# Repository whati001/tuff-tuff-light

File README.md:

# 🚜 Wireless BLE Trailer Light System for Tractors

A robust, modular, and completely wireless trailer lighting system designed for agricultural machinery, utilizing BLE communication. 
Built on the **nRF52840 SoC** and developed with the **Zephyr RTOS**, this project includes custom-designed PCBs and 3D printed enclosures for reliable field use.
The choose design enables seamless connectivity without complicated pairing procedures and also allows to connect up to infinite receiver lights to a single sender.  

## ✨ Features

- 🔋 Battery-powered light modules (18650 x 4)
- 📡 BLE-based communication (nRF52840)
- 🔧 Built with **Zephyr RTOS**
- 🔦 Fully functional red+amber light cluster with wireless control
- 🧲 Magnetic mounting for quick install/removal
- 💻 Custom 3D printed cases and two custom-designed PCBs
- 🧠 Intelligent Power Saving (auto wakeup, no need to "switch" the light on)
---

## 📦 Project Structure
The project is structured as follows.
```
.
├── 3d/             # 3d printer files
├── applications/ 
│ ├── ttl_sender/   # ttl sender code
│ └── ttl_receiver/ # ttl receiver code
├── boards/         # custom boards definition
├── pcb/            # custom pcb KiCad files
...
└── README.md
```

---

## 🚀 Getting Started

### 🛠️ Requirements

- [Zephyr SDK](https://docs.zephyrproject.org/latest/develop/getting_started/index.html)
- [West Tool](https://docs.zephyrproject.org/latest/develop/west/index.html)
- Python 3.8+
- USB debugger (J-Link or compatible)
- Custom PCB (JLC PCB + self assembly)

### 📥 1. Clone and Initialize
First we need to initiate a python environment and install west. Afterwards, we initiate the Zephyr workspace.
```bash
python -m venv ./env
<activate venv>
pip install west
west init -m https://github.com/whati001/tuff-tuff-light tuff_tuff_light
cd tuff_tuff_light
west update
```

### 🧪 2. Build the Firmware
Navigate into the workspace directory and run:

```
# build sender
west build -b ttlv1_pa/nrf52840 ttl/applications/ttl_sender

# build receiver
west build -b ttlv1/nrf52840 ttl/applications/ttl_sender
```

### 🔌 3. Flash the Devices

Connect your debugger and run:

```
west flash
```

## 📡 System Overview

Transmitter: Reads trailer socket signals and broadcasts light commands via BLE.
Receiver Modules: Interpret BLE commands and control LEDs accordingly.

## 🧩 Hardware Details

* PCBs
  * TX Board: Reads 4-pin trailer plug input, handles BLE communication.
  * RX Board: Contains BLE radio, LED drivers, battery power management.

* Enclosures
  * All parts are printed with PLA and designed for rugged outdoor use.
  * STL/STEP files are included in the 3d/ directory.

## 🧪 Testing and Validation

The project aims just to be a minimal viable project (MVP), so there is not much testing included.

## 📃 License

This project is licensed under the MIT License. See the LICENSE file for details.

## 🤝 Contributing

Contributions are welcome! If you'd like to add features (e.g., low battery warnings, OTA updates), feel free to open a PR or issue.
If you are interested to turn this MVP into a real project, please get in touch with me. 

## 🧭 Next Steps

Here are a few ideas and enhancements planned or recommended for future development:

🔋 Battery Charging
Currently, power is restored by manually replacing the 18650 batteries. The proposed improvement is to integrate a charging circuit directly into the 3D-printed enclosure, enabling in-place recharging and eliminating the need to open the housing. At the same time, the design would retain compatibility with swappable battery modules, allowing a quick base replacement in scenarios where charging time is a limiting factor.

🚦 Expanded Signal Set
Extend support for additional signal inputs from the standard 7-pin trailer connector, including reverse, brake, fog lights, and more. Furthermore, the system’s modular architecture enables the integration of entirely new light types, such as side marker lights (e.g., white delimiting lights along the trailer’s sides), enhancing both functionality and visibility.

🌧️ Weatherproofing Enhancements
Improve gasket seals in the 3D printed case and verify IP rating in outdoor environments.

📘 Documentation Expansion
Add detailed firmware architecture docs and schematic walkthroughs.

## 📬 Contact

For questions, suggestions, or demo requests, feel free to contact [whati001@outlook.com] or open a GitHub issue

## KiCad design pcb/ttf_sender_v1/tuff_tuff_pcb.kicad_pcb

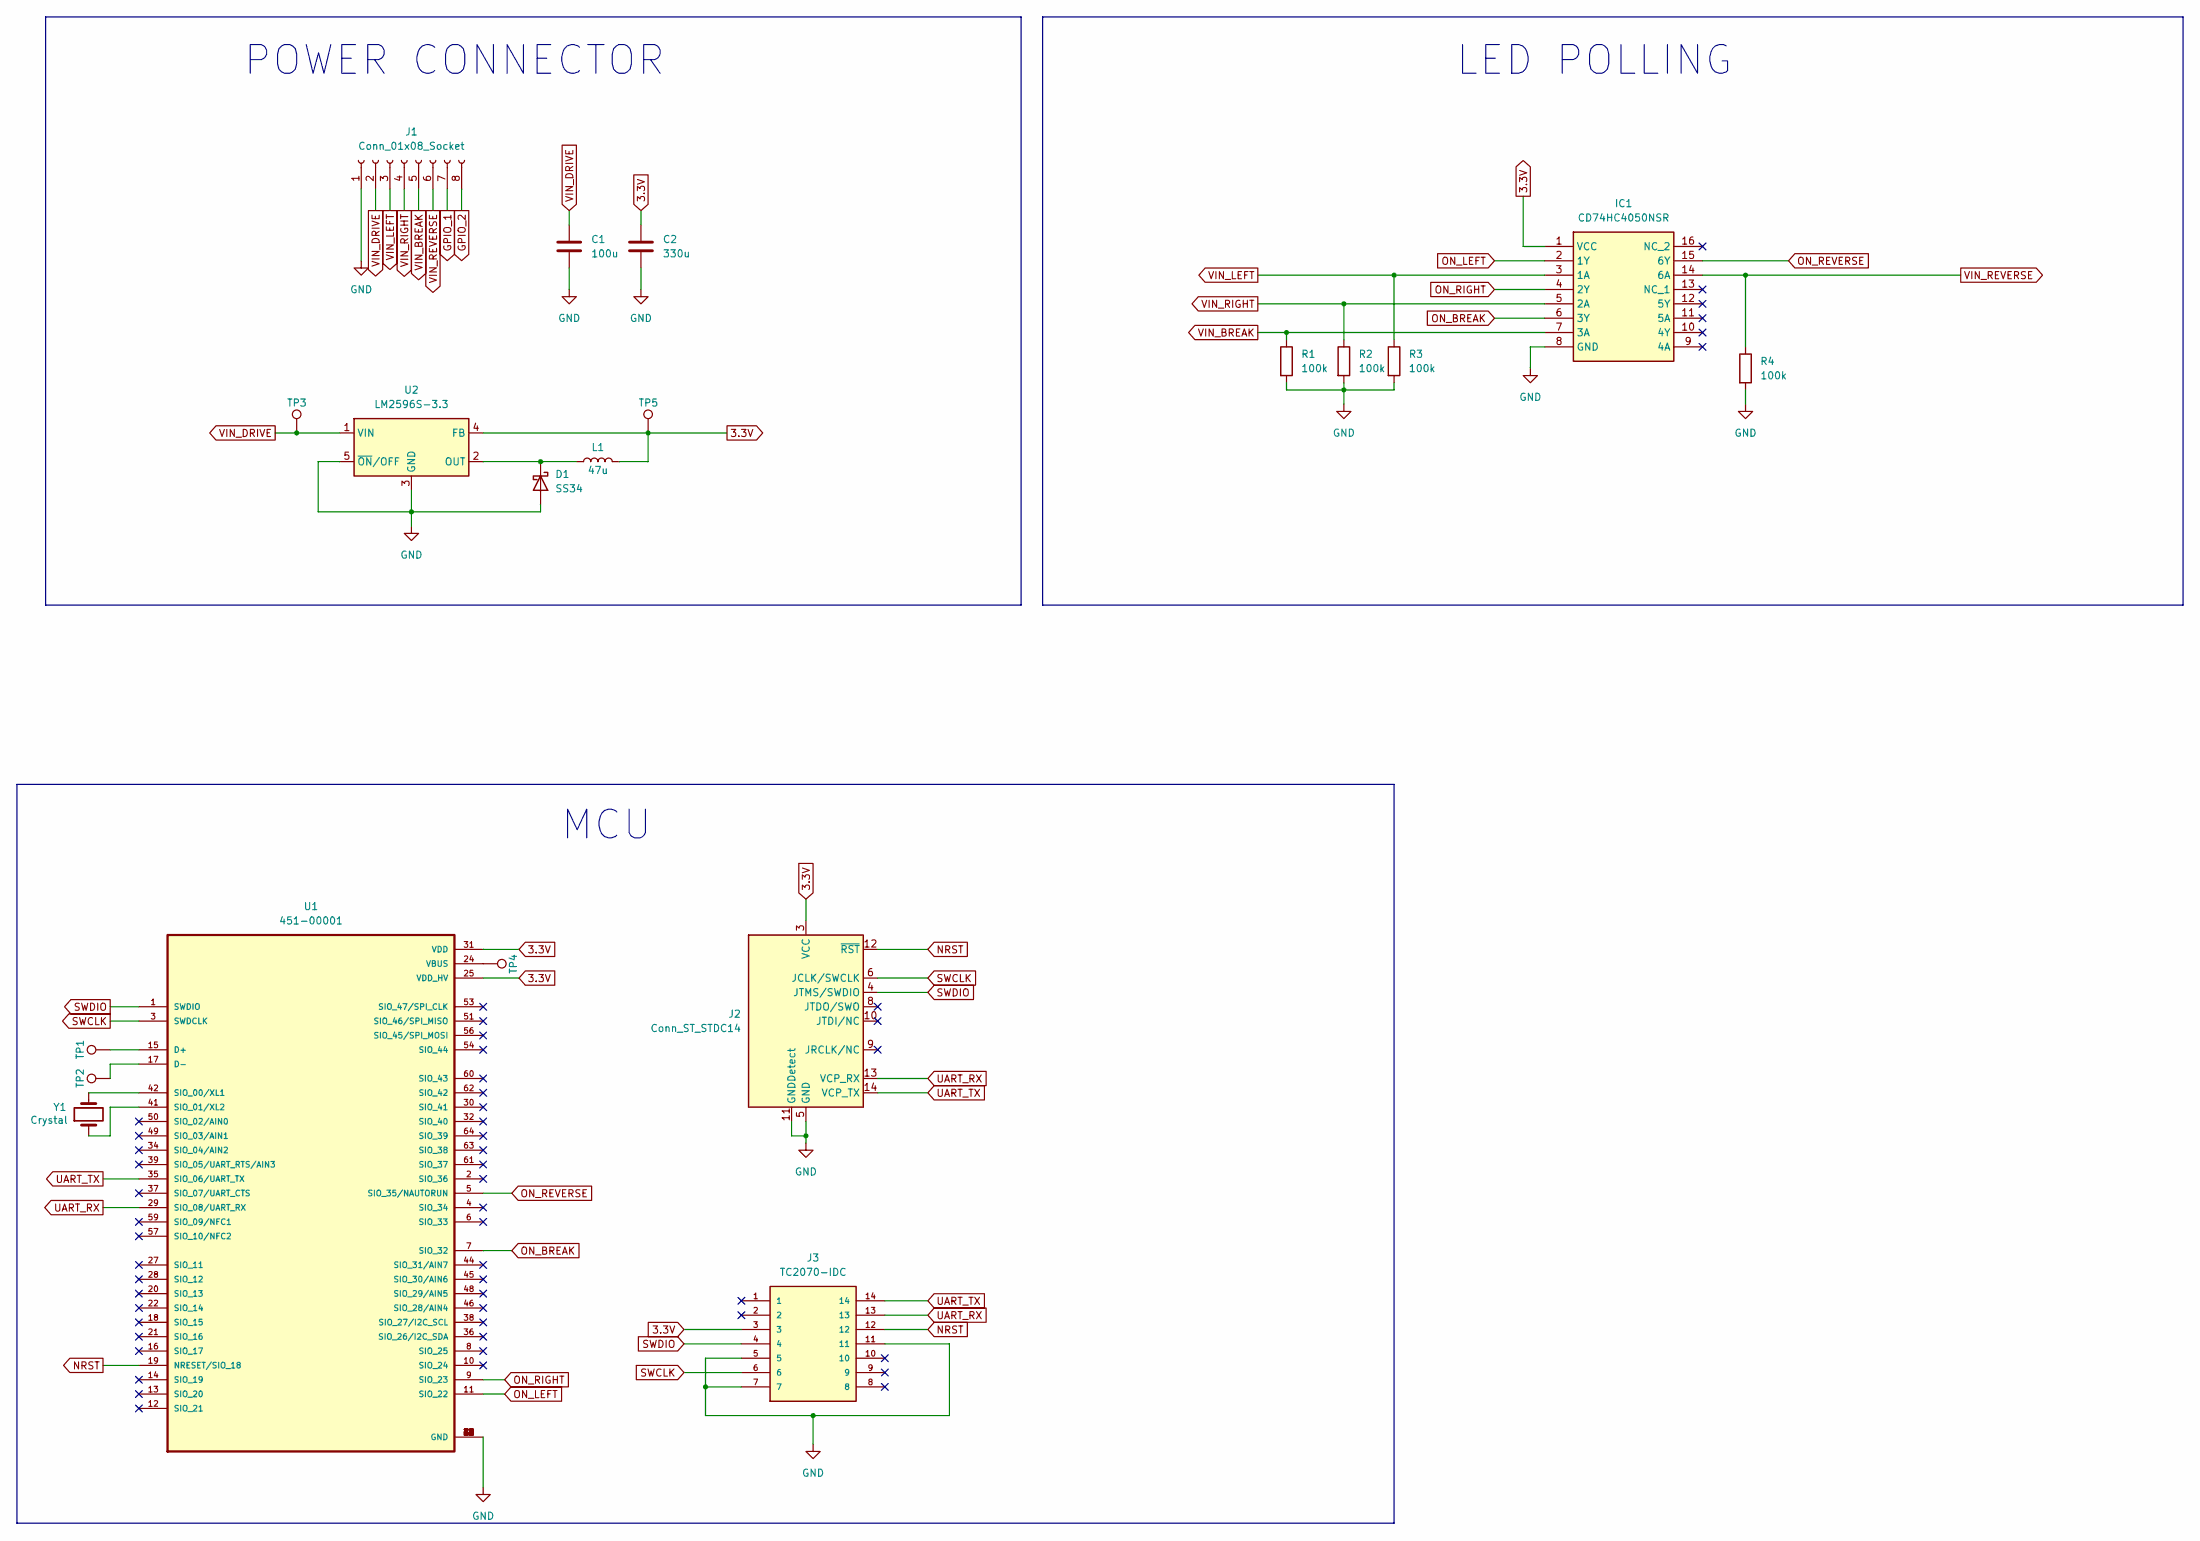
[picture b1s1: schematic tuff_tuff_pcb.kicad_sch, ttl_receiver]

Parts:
C1: 100u; CP_Radial_D5.0mm_P2.00mm; Part# at home
C2: 330u; CP_Radial_D8.0mm_P3.80mm; Part# at home
D1: SS34; D_SMA; LCSC C8678
IC1: CD74HC4050NSR; TSSOP-16_4.4x5mm_P0.65mm; Mouser Part Number 595-CD74HC4050NSR
J1: Conn_01x08_Socket; PinHeader_1x08_P2.00mm_Vertical
J2: Conn_ST_STDC14; PinHeader_2x07_P1.27mm_Vertical_SMD; LCSC C41370775
J3: TC2070-IDC; TAG-CONNECT_TC2070-IDC
L1: 47u; L_12x12mm_H8mm; LCSC C2041853
R1, R2, R3: 100k; C_1206_3216Metric_Pad1.33x1.80mm_HandSolder; LCSC C17900
R4: 100k; C_1206_3216Metric_Pad1.33x1.80mm_HandSolder; LCSC Part# C4107364
TP1, TP2, TP3, TP4, TP5: TestPoint; TestPoint_Pad_D2.0mm
U1: 451-00001; XCVR_451-00001; Mouser Part# 814-451-00002
U2: LM2596S-3.3; TO-263-5_TabPin3; LCSC C5186052
Y1: Crystal; Crystal_SMD_MicroCrystal_CC8V-T1A-2Pin_2.0x1.2mm; Mouser Part# 428-201410-MC01

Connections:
3.3V: C2.1, IC1.1 (VCC), J2.3 (VCC), J3.3, L1.2, TP5.1, U1.25 (VDD_HV), U1.31 (VDD), U2.4 (FB)
GND: C1.2, C2.2, D1.2 (A), IC1.8 (GND), J1.1, J2.5 (GND), J2.7 (GND), J2.11 (GNDDetect), J3.5, J3.7, J3.11, R1.2, R2.2, R3.2, R4.2, U1.0 (GND), U1.23 (GND), U1.26 (GND), U1.33 (GND), U1.40 (GND), U1.43 (GND), U1.47 (GND), U1.52 (GND), U1.55 (GND), U1.58 (GND), U1.65 (GND), U1.66 (GND), U1.67 (GND), U1.68 (GND), U1.69 (GND), U1.70 (GND), U1.71 (GND), U2.3 (GND), U2.5 (~ON/OFF)
GPIO_1: J1.7
GPIO_2: J1.8
NRST: J2.12 (~RST), J3.12, U1.19 (NRESET/SIO_18)
unnamed: D1.1 (K), L1.1, U2.2 (OUT)
unnamed: TP1.1, U1.15 (D+)
unnamed: TP2.1, U1.17 (D-)
unnamed: U1.42 (SIO_00/XL1), Y1.2
unnamed: U1.41 (SIO_01/XL2), Y1.1
unnamed: TP4.1, U1.24 (VBUS)
ON_BREAK: IC1.6 (3Y), U1.7 (SIO_32)
ON_LEFT: IC1.2 (1Y), U1.11 (SIO_22)
ON_REVERSE: IC1.15 (6Y), U1.5 (SIO_35/NAUTORUN)
ON_RIGHT: IC1.4 (2Y), U1.9 (SIO_23)
SWCLK: J2.6 (JCLK/SWCLK), J3.6, U1.3 (SWDCLK)
SWDIO: J2.4 (JTMS/SWDIO), J3.4, U1.1 (SWDIO)
UART_RX: J2.13 (VCP_RX), J3.13, U1.29 (SIO_08/UART_RX)
UART_TX: J2.14 (VCP_TX), J3.14, U1.35 (SIO_06/UART_TX)
VIN_BREAK: IC1.7 (3A), J1.5, R1.1
VIN_DRIVE: C1.1, J1.2, TP3.1, U2.1 (VIN)
VIN_LEFT: IC1.3 (1A), J1.3, R3.1
VIN_REVERSE: IC1.14 (6A), J1.6, R4.1
VIN_RIGHT: IC1.5 (2A), J1.4, R2.1

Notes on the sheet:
MCU
LED POLLING
POWER CONNECTOR

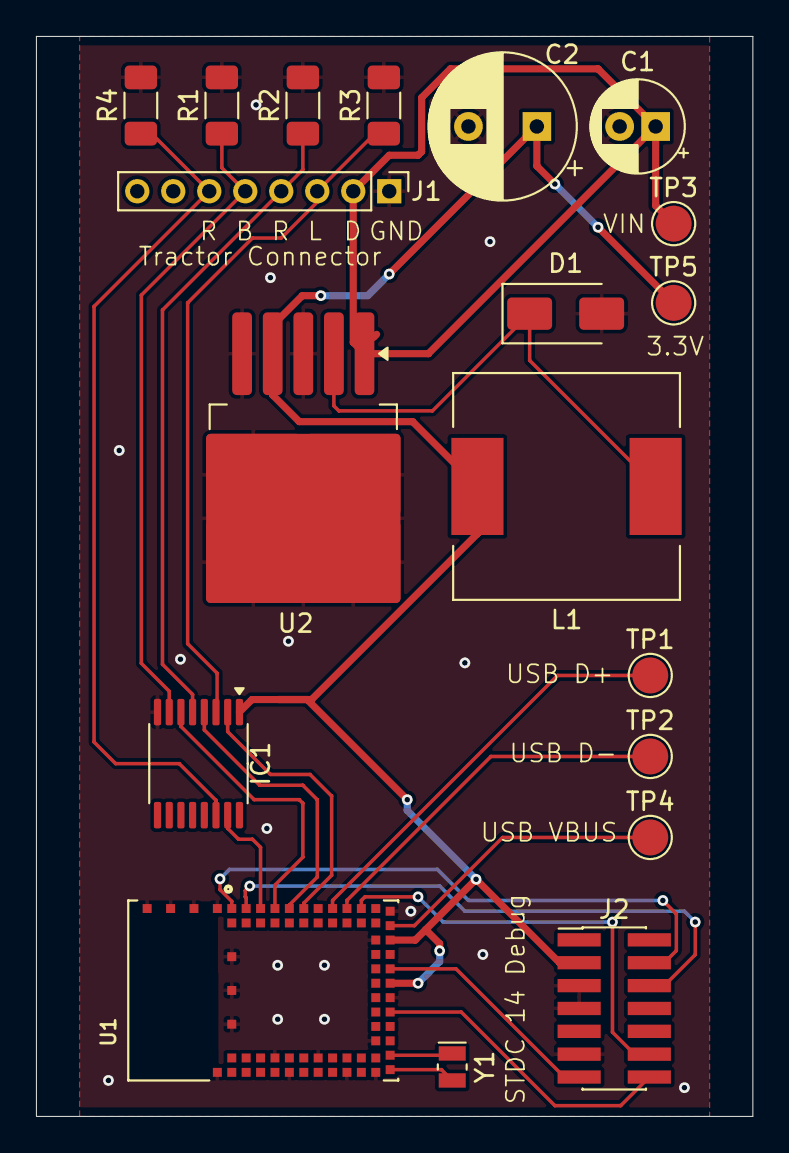
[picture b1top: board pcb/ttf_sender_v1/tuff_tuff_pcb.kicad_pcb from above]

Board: 2 copper layers, 39.8 x 60.0 mm, 19 parts (0 on the bottom side), 22 nets.

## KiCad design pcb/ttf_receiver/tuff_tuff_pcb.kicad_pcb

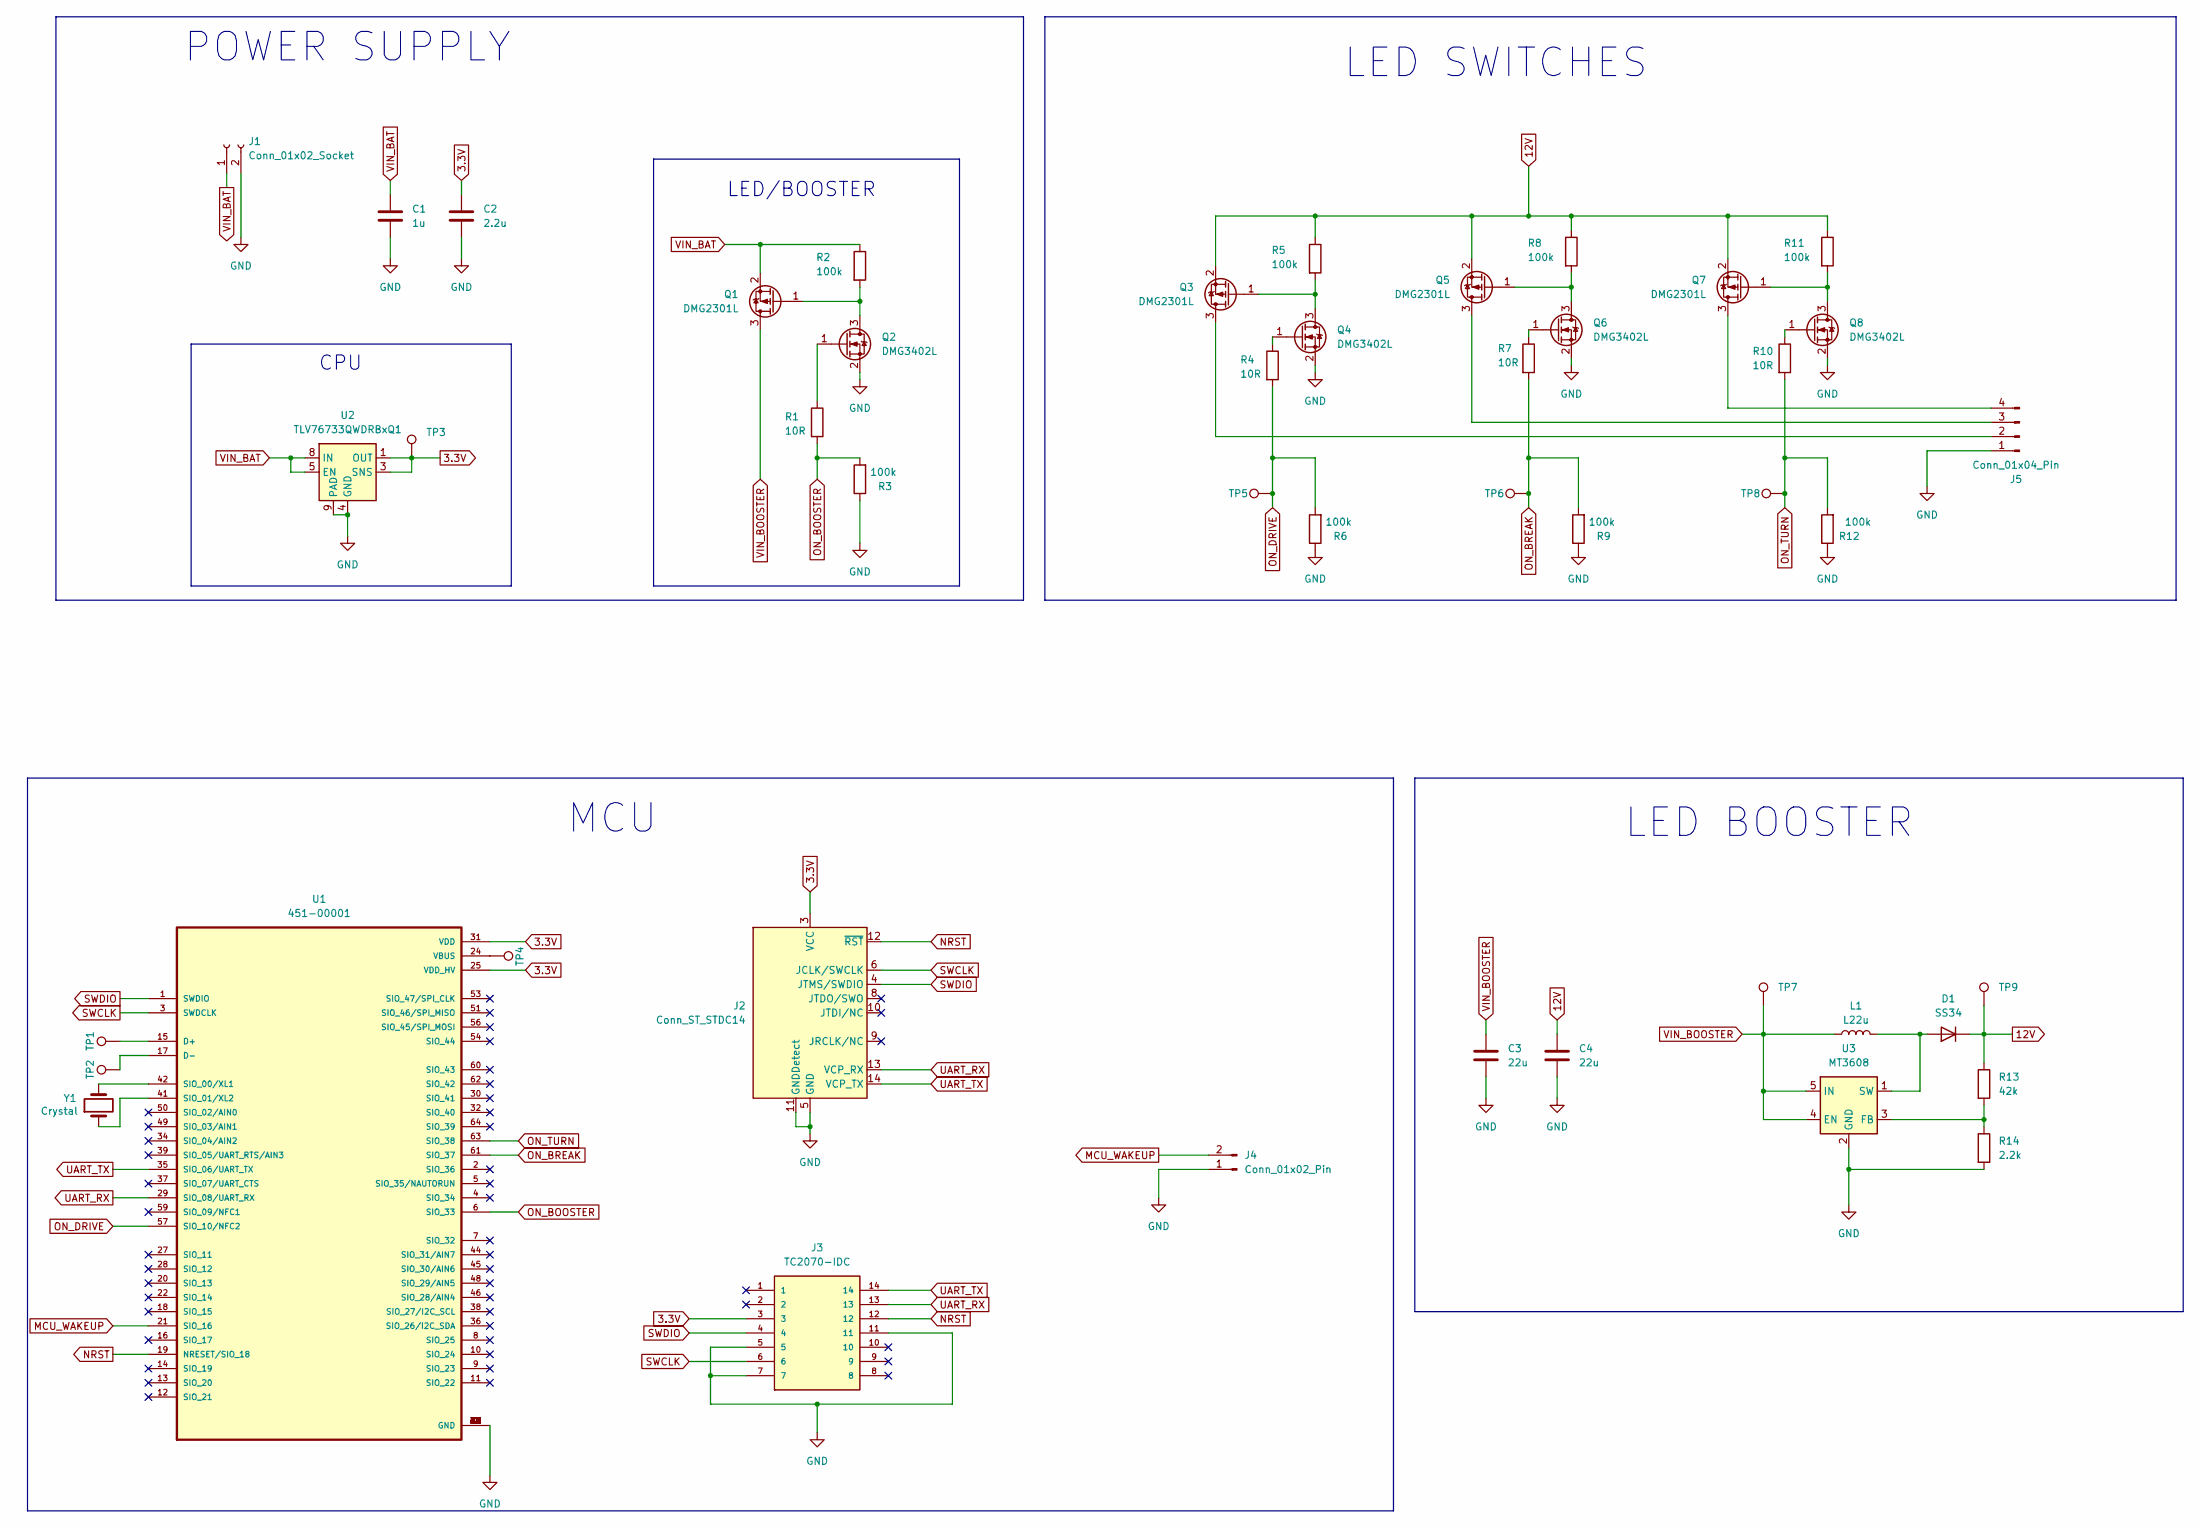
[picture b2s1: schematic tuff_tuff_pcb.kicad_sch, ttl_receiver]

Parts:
C1: 1u; C_1206_3216Metric_Pad1.33x1.80mm_HandSolder; LCSC C1848
C2: 2.2u; C_1206_3216Metric_Pad1.33x1.80mm_HandSolder; LCSC C50254
C3, C4: 22u; C_1206_3216Metric_Pad1.33x1.80mm_HandSolder; LCSC C12891
D1: SS34; D_SMA; LCSC C8678
J1: Conn_01x02_Socket; PinHeader_1x02_P2.54mm_Vertical
J2: Conn_ST_STDC14; PinHeader_2x07_P1.27mm_Vertical_SMD; LCSC C41370775
J3: TC2070-IDC; TAG-CONNECT_TC2070-IDC
J4: Conn_01x02_Pin; PinSocket_1x02_P2.54mm_Vertical
J5: Conn_01x04_Pin; PinHeader_1x04_P2.54mm_Vertical
L1: L22u; L_1210_3225Metric; LCSC C711136
Q1, Q3, Q5, Q7: DMG2301L; SOT-23; LCSC C102619
Q2, Q4, Q6, Q8: DMG3402L; SOT-23; LCSC C96614
R1, R4, R7, R10: 10R; R_1206_3216Metric_Pad1.30x1.75mm_HandSolder; LCSC C104606
R2, R3, R5, R6, R8, R9, R11, R12: 100k; R_1206_3216Metric_Pad1.30x1.75mm_HandSolder; LCSC C17900
R13: 42k; R_1206_3216Metric_Pad1.30x1.75mm_HandSolder; LCSC C229633
R14: 2.2k; R_1206_3216Metric_Pad1.30x1.75mm_HandSolder; LCSC C114933
TP1, TP2, TP3, TP4, TP5, TP6, TP8: TestPoint; TestPoint_Pad_D2.0mm
TP7: IN BOOSTER; TestPoint_Pad_D2.0mm
TP9: OUT BOOSTER; TestPoint_Pad_D2.0mm
U1: 451-00001; XCVR_451-00001; Mouser Part# 814-451-00002
U2: TLV76733QWDRBxQ1; SOP65P490X110-9N; LCSC C2873382
U3: MT3608; SOT-23-6; LCSC C84817
Y1: Crystal; Crystal_SMD_MicroCrystal_CC8V-T1A-2Pin_2.0x1.2mm; Mouser Part# 428-201410-MC01

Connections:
3.3V: C2.1, J2.3 (VCC), J3.3, TP3.1, U1.25 (VDD_HV), U1.31 (VDD), U2.1 (OUT), U2.3 (SNS)
12V: C4.1, D1.1 (K), Q3.2 (S), Q5.2 (S), Q7.2 (S), R5.1, R8.1, R11.1, R13.1, TP9.1
GND: C1.2, C2.2, C3.2, C4.2, J1.2, J2.5 (GND), J2.7 (GND), J2.11 (GNDDetect), J3.5, J3.7, J3.11, J4.1, J5.1, Q2.2 (S), Q4.2 (S), Q6.2 (S), Q8.2 (S), R3.1, R6.1, R9.1, R12.1, R14.2, U1.0 (GND), U1.23 (GND), U1.26 (GND), U1.33 (GND), U1.40 (GND), U1.43 (GND), U1.47 (GND), U1.52 (GND), U1.55 (GND), U1.58 (GND), U1.65 (GND), U1.66 (GND), U1.67 (GND), U1.68 (GND), U1.69 (GND), U1.70 (GND), U1.71 (GND), U2.4 (GND), U2.6 (GND), U2.9 (PAD), U3.2 (GND)
MCU_WAKEUP: J4.2, U1.21 (SIO_16)
NRST: J2.12 (~RST), J3.12, U1.19 (NRESET/SIO_18)
unnamed: D1.2 (A), L1.2, U3.1 (SW)
unnamed: J5.2, Q3.3 (D)
unnamed: J5.3, Q5.3 (D)
unnamed: J5.4, Q7.3 (D)
unnamed: Q1.1 (G), Q2.3 (D), R2.2
unnamed: Q2.1 (G), R1.1
unnamed: Q3.1 (G), Q4.3 (D), R5.2
unnamed: Q4.1 (G), R4.1
unnamed: Q5.1 (G), Q6.3 (D), R8.2
unnamed: Q6.1 (G), R7.1
unnamed: Q7.1 (G), Q8.3 (D), R11.2
unnamed: Q8.1 (G), R10.1
unnamed: TP1.1, U1.15 (D+)
unnamed: TP2.1, U1.17 (D-)
unnamed: U1.42 (SIO_00/XL1), Y1.2
unnamed: U1.41 (SIO_01/XL2), Y1.1
unnamed: TP4.1, U1.24 (VBUS)
unnamed: R13.2, R14.1, U3.3 (FB)
ON_BOOSTER: R1.2, R3.2, U1.6 (SIO_33); also elsewhere on the board
ON_BREAK: R7.2, R9.2, TP6.1, U1.61 (SIO_37)
ON_DRIVE: R4.2, R6.2, TP5.1, U1.57 (SIO_10/NFC2)
ON_TURN: R10.2, R12.2, TP8.1, U1.63 (SIO_38)
SWCLK: J2.6 (JCLK/SWCLK), J3.6, U1.3 (SWDCLK)
SWDIO: J2.4 (JTMS/SWDIO), J3.4, U1.1 (SWDIO)
UART_RX: J2.13 (VCP_RX), J3.13, U1.29 (SIO_08/UART_RX)
UART_TX: J2.14 (VCP_TX), J3.14, U1.35 (SIO_06/UART_TX)
VIN_BAT: C1.1, J1.1, Q1.2 (S), R2.1, U2.5 (EN), U2.8 (IN)
VIN_BOOSTER: C3.1, L1.1, Q1.3 (D), TP7.1, U3.4 (EN), U3.5 (IN)

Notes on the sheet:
LED/BOOSTER
LED BOOSTER
MCU
CPU
LED SWITCHES
POWER SUPPLY

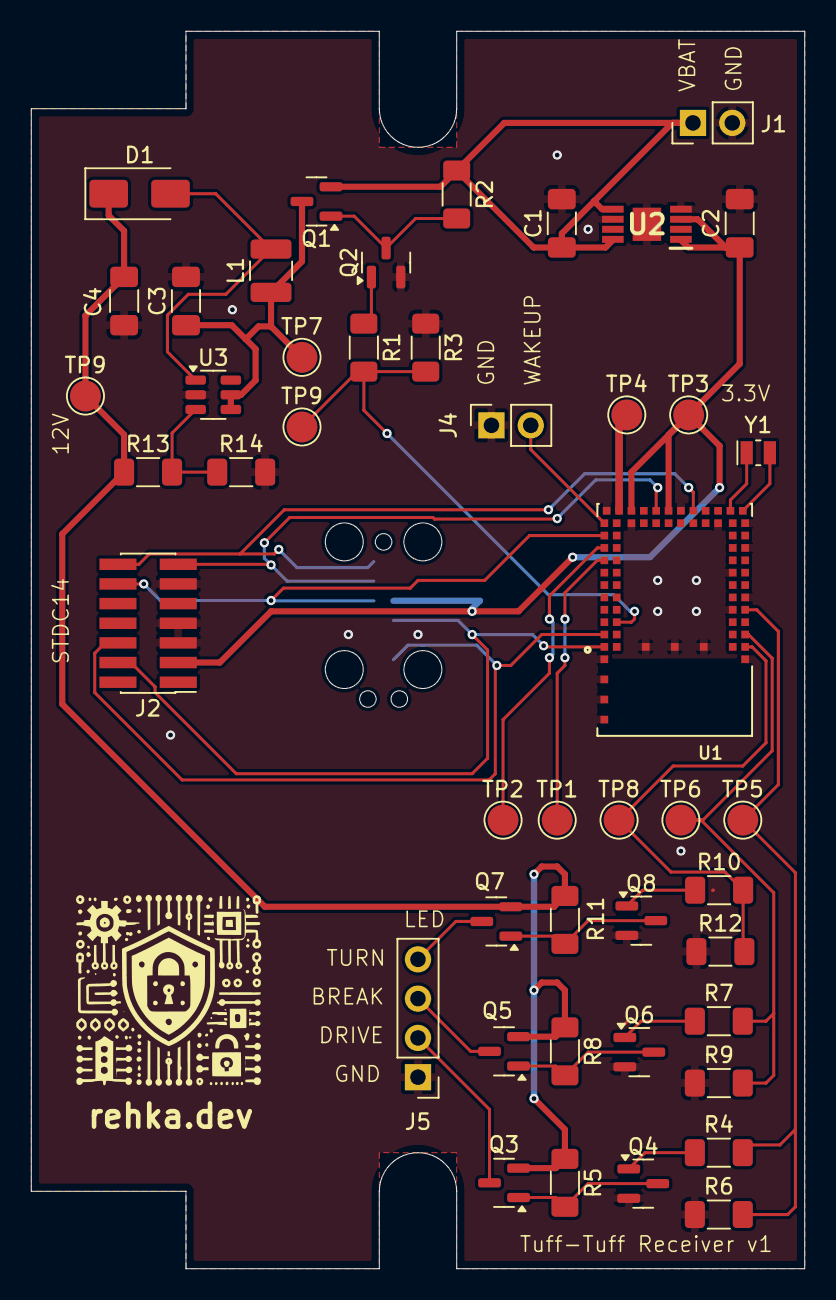
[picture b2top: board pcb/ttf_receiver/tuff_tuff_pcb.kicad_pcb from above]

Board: 2 copper layers, 50.0 x 80.0 mm, 47 parts (1 on the bottom side), 33 nets.

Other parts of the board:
TP9#2: ON BOOSTER; TestPoint_Pad_D2.0mm

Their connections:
ON_BOOSTER: TP9#2.1; also elsewhere on the board

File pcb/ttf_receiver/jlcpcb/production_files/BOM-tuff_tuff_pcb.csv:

Comment,Designator,Footprint,LCSC,Quantity
DMG2301L,"Q1,Q3,Q5,Q7",SOT-23,C102619,4
10R,"R1,R10,R4,R7",R_1206_3216Metric_Pad1.30x1.75mm_HandSolder,C104606,4
2.2k,R14,R_1206_3216Metric_Pad1.30x1.75mm_HandSolder,C114933,1
22u,"C3,C4",C_1206_3216Metric_Pad1.33x1.80mm_HandSolder,C12891,2
100k,"R11,R12,R2,R3,R5,R6,R8,R9",R_1206_3216Metric_Pad1.30x1.75mm_HandSolder,C17900,8
1u,C1,C_1206_3216Metric_Pad1.33x1.80mm_HandSolder,C1848,1
42k,R13,R_1206_3216Metric_Pad1.30x1.75mm_HandSolder,C229633,1
TLV76733QWDRBxQ1,U2,SOP65P490X110-9N,C2873382,1
Conn_ST_STDC14,J2,PinHeader_2x07_P1.27mm_Vertical_SMD,C41370775,1
2.2u,C2,C_1206_3216Metric_Pad1.33x1.80mm_HandSolder,C50254,1
Crystal,Y1,Crystal_SMD_MicroCrystal_CC8V-T1A-2Pin_2.0x1.2mm,C5142652,1
L22u,L1,L_1210_3225Metric,C711136,1
451-00001,U1,XCVR_451-00001,C7185357,1
MT3608,U3,SOT-23-6,C84817,1
SS34,D1,D_SMA,C8678,1
DMG3402L,"Q2,Q4,Q6,Q8",SOT-23,C96614,4
ON BOOSTER,TP9,TestPoint_Pad_D2.0mm,,1

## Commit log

2022-01-06 AK - added digital read
2022-01-07 AK - added cad and cleaned code
2022-01-07 AK - removed build
2022-01-07 AK - added build dir to gitignore
2022-01-08 AK - added peripheral dk poc code
2022-01-08 AK - renamed stage to state
2022-01-08 AK - added central poc code
2022-01-10 AK - added central interrupt listener
2022-01-11 AK - added interrupt support on central
2022-01-11 AK - disable some logging
2022-01-11 AK - added nrf52840dongle board overlay
2022-01-11 AK - added multilink
2022-01-11 AK - fixed issue6 use polling with 50ms interval on central
2022-01-29 AK - added vscode config and sourced out include files
2022-09-21 AK - refactored peripheral
2022-09-21 AK - added NO_HOST_STATE update to prevent wrong signals on the leds
2022-09-27 AK - added stuff
2022-09-29 AK - something
2022-10-19 AK - added batch
2023-07-11 AK - added some code which allows us to send data via a single ISO channel
2023-07-11 AK - first BLE ISO broadcaster code for the controller
2023-07-12 AK - added POC code of controller
2023-07-12 AK - added some POC magic values
2023-07-12 AK - added some crapy receive code
2023-07-12 AK - added POC with iso channels
2023-07-12 AK - removed old stuff
2023-07-14 AK - changed logic to send pin state not final mapped state
2023-07-14 AK - added white channel
2023-08-17 AK - added separate BREAK light
2023-08-28 AK - added working pwm code
2023-08-28 AK - extended code to support four different pwm channels
2023-09-21 AK - updated project
2023-11-19 refactor(dt): Updated devicetree files for nrf-dk and nrf-dongle
2023-11-19 docs: Added schematic and gerber files
2023-11-19 feat: Added accelerometer assembly test
2023-11-19 feat(dt): Fixed devicetree file to adxl345 on dk
2023-11-20 added debug support
2023-12-01 test: Added accelerator test code
2023-12-01 feat: Added accel support
2023-12-03 feat: Added poweroff feature with accel wakeup.
2023-12-04 feat: Added feature to shutdown device if no signal was received for CONFIG_TTL_SHUTDOWN_TIMEOUT
2023-12-04 refactor: Refactored code to use new zephyr sensor api.
2023-12-08 feat: Refactored code to work with updated zephyr code and pushed to first ttl release version.
2023-12-10 refactor(dt): Refactored code and ajdusted dt file for broadcaster dk.
2023-12-14 fix: Removed reverse because the plug does not provide this information.
2023-12-17 perf: Optimized timeout value.
2023-12-17 docs: added datasheets
2024-01-05 fix: Increased ble signal strength
2024-01-07 perf: Rewritten sender to use periodic advertisement instead of iso channels.
2024-01-07 refactor: Renamed iso_receiver to ttl_receiver
2024-01-07 refactor: Removed dead code and updated function description
2024-01-07 refactor: Rewritten receiver to use periodic sync
2024-01-07 refactor: Rewritten receiver to use periodic adv instead of iso channels
2024-01-07 refactor: Updated printk to LOG_INF and decreased sleep time.
2024-01-07 fix: Reduced BLE periodic advertise time significantly.
2024-01-07 refactor: Simplified logic to start thread in start and kill it in stop instead of hitting a lock quite often
2024-02-11 refactor: Reactivated accel.
2024-02-11 feat(dt): Added dt files for connectkit
2024-02-27 feat: Use normal BLE
2024-03-01 feat: Moved sender back to use iso channels
2024-03-01 feat: Changed receiver back to iso channels
2024-05-01 updated stuff
2024-05-01 mass update
2024-05-01 Limit ttl state print via Kconfig option
2024-05-01 updated receiver
2024-05-08 updated receiver code
2024-05-20 update ble iso receive code
2024-05-20 fixed callback
2024-05-20 Fixed polling interval
2024-05-26 updated code for connectkit_nrf52840
2024-05-26 connectsdk changes
2024-06-04 fix: Remapped accel i2c pins for connectkit_nrf52840
2024-06-07 remapped holydongle pins to something
2024-06-07 refactor: Refactored receiver and sender code (#16)
2024-06-07 fix: Receiver wake up for movements right after sleep
2024-06-07 fix: Corrected holy iot dongle gpio mapping
2024-08-05 fix: Corrected ttl sender overlay for holyiot board
2024-08-05 feat: Added LDO datasheet used by ttl receiver
2024-09-24 test(dt): Added regulator devicetree node
2025-01-18 feat(pcb): Added kicad files for receiver and sender
2025-03-01 feat: Added ttl sender v1 board definition
2025-03-01 feat: Added west manifest file
2025-03-01 feat: Added initial ttl sender and receiver code
2025-03-01 chore: Added licence file
2025-03-01 feat: Added version 1 pcb kicad files
2025-03-09 chore: Updated gitignore file
2025-03-09 feat: Added new ttl board definition
2025-03-09 feat: Ported ttl receiver to new board
2025-03-09 feat: Updated ttl schematic
2025-03-10 feat: Updated ttl receiver code to match new zephyr iso channel and run on nrf52840dk
2025-03-10 feat: Updated ttl sender code to match new zephyr iso sample
2025-03-14 feat(receiver): Use internal LF crystal
2025-03-14 fix(sender): Updated sender code to work again
2025-06-22 fix: Updated board overlay files
2025-06-23 feat: Added receiver case stl file
2025-06-23 doc: Update readme document
2025-08-02 docs: Added demonstration video to readme
